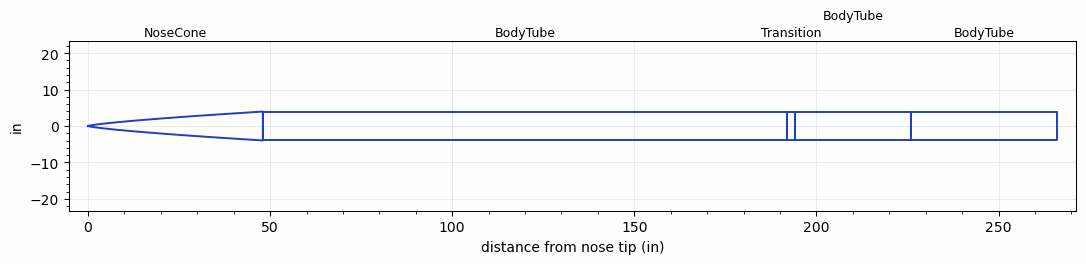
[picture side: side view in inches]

<RASAeroDocument>
 <FileVersion>2</FileVersion>
 <RocketDesign>
  <NoseCone>
   <Length>48</Length>
   <Diameter>7.927</Diameter>
   <Shape>Power Law</Shape>
   <Location>0</Location>
   <PowerLaw>0.75</PowerLaw>
  </NoseCone>
  <BodyTube>
   <Length>144</Length>
   <Diameter>7.927</Diameter>
   <Location>48</Location>
  </BodyTube>
  <Transition>
   <Length>2</Length>
   <Diameter>7.926</Diameter>
   <Location>192</Location>
   <RearDiameter>7.926</RearDiameter>
  </Transition>
  <BodyTube>
   <Length>32</Length>
   <Diameter>7.926</Diameter>
   <Location>194</Location>
  </BodyTube>
  <BodyTube>
   <Length>40</Length>
   <Diameter>7.926</Diameter>
   <Location>226</Location>
  </BodyTube>
  <Surface>Smooth (Zero Roughness)</Surface>
  <ModifiedBarrowman>False</ModifiedBarrowman>
  <Turbulence>False</Turbulence>
  <SustainerNozzle>7.5</SustainerNozzle>
  <UseBooster1>False</UseBooster1>
  <UseBooster2>False</UseBooster2>
 </RocketDesign>
 <LaunchSite>
  <Altitude>0</Altitude>
  <Pressure>0</Pressure>
  <RodAngle>0</RodAngle>
  <RodLength>4</RodLength>
  <Temperature>74</Temperature>
  <WindSpeed>5</WindSpeed>
 </LaunchSite>
 <Recovery>
  <Altitude1>1000</Altitude1>
  <Altitude2>1000</Altitude2>
  <DeviceType1>Parachute</DeviceType1>
  <DeviceType2>None</DeviceType2>
  <Event1>True</Event1>
  <Event2>False</Event2>
  <Size1>4</Size1>
  <Size2>1</Size2>
  <EventType1>Apogee</EventType1>
  <EventType2>None</EventType2>
  <CD1>1.33</CD1>
  <CD2>1.33</CD2>
 </Recovery>
 <MachAlt>
  <Item>5, 100000</Item>
 </MachAlt>
 <SimulationList>
  <Simulation>
   <SustainerEngine>Q18000  (DEAP-EX)</SustainerEngine>
   <SustainerLaunchWt>160</SustainerLaunchWt>
   <SustainerNozzleDiameter>7.5</SustainerNozzleDiameter>
   <SustainerCG>60</SustainerCG>
   <SustainerIgnitionDelay>0.5</SustainerIgnitionDelay>
   <Booster1SeparationDelay>0</Booster1SeparationDelay>
   <Booster1IgnitionDelay>0</Booster1IgnitionDelay>
   <IncludeBooster1>False</IncludeBooster1>
   <Booster2Delay>0</Booster2Delay>
   <IncludeBooster2>False</IncludeBooster2>
   <MaxVelocity>21.84772</MaxVelocity>
   <OptimumWt>138</OptimumWt>
   <OptimumMaxAlt>138</OptimumMaxAlt>
  </Simulation>
 </SimulationList>
</RASAeroDocument>
